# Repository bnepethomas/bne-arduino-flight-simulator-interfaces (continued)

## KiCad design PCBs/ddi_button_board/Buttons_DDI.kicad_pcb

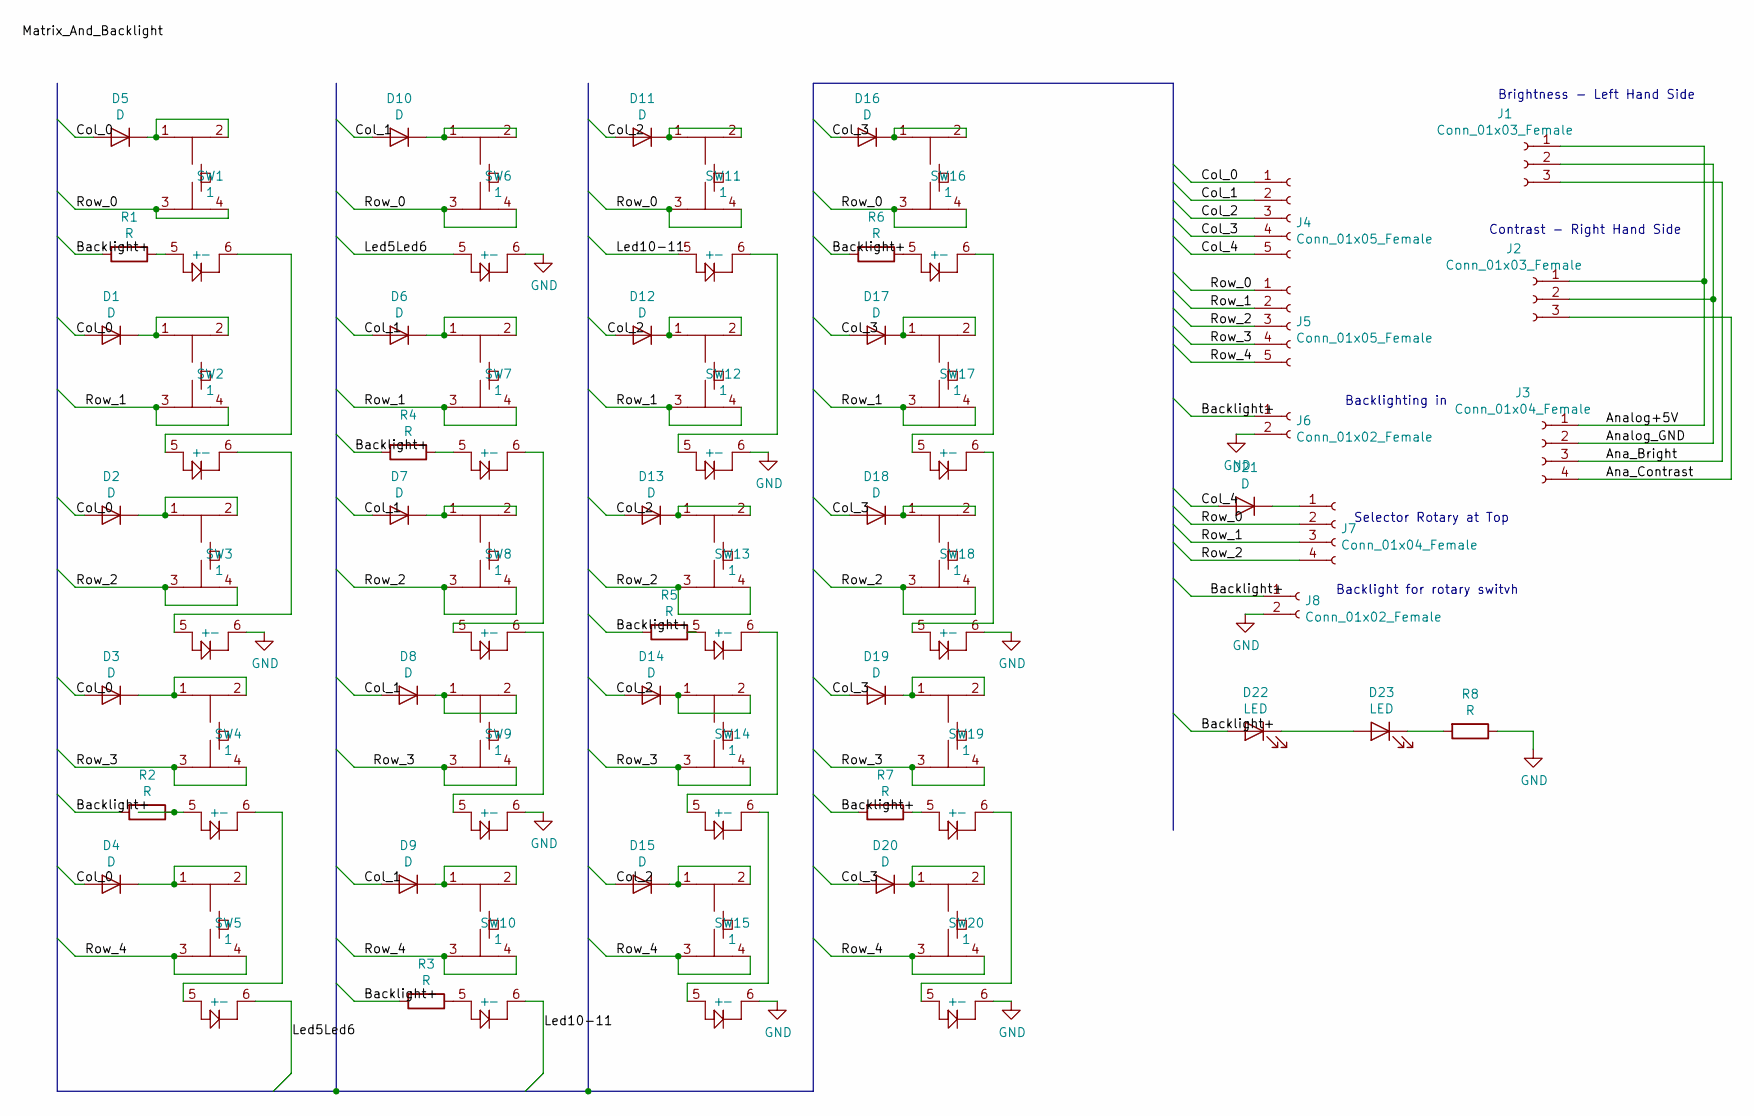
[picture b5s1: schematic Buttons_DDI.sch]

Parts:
D1, D2, D3, D4, D5, D6, D7, D8, D9, D10, D11, D12, D13, D14, D15, D16, D17, D18, D19, D20, D21: D; D_A-405_P7.62mm_Horizontal
D22, D23: LED; LED_D3.0mm
J1, J2: Conn_01x03_Female; PinHeader_1x03_P2.54mm_Vertical
J3, J7: Conn_01x04_Female; PinHeader_1x04_P2.54mm_Vertical
J4, J5: Conn_01x05_Female; PinHeader_1x05_P2.54mm_Vertical
J6, J8: Conn_01x02_Female; PinHeader_1x02_P2.54mm_Vertical
R1, R2, R3, R4, R5, R6, R7, R8: R; R_Axial_DIN0207_L6.3mm_D2.5mm_P7.62mm_Horizontal
SW1, SW2, SW3, SW4, SW5, SW6, SW7, SW8, SW9, SW10, SW11, SW12, SW13, SW14, SW15, SW16, SW17, SW18, SW19, SW20: 1; PT_Small_Tactile_Switch_With_LED

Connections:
/Ana_Bright: J1.3, J3.3
/Ana_Contrast: J2.3, J3.4
/Analog+5V: J1.1, J2.1, J3.1
/Analog_GND: J1.2, J2.2, J3.2
/Backlight+: D22.2 (A), J6.1, J8.1, R1.2, R2.2, R3.2, R4.2, R5.2, R6.2, R7.2
/Col_0: D1.2 (A), D2.2 (A), D3.2 (A), D4.2 (A), D5.2 (A), J4.1
/Col_1: D6.2 (A), D7.2 (A), D8.2 (A), D9.2 (A), D10.2 (A), J4.2
/Col_2: D11.2 (A), D12.2 (A), D13.2 (A), D14.2 (A), D15.2 (A), J4.3
/Col_3: D16.2 (A), D17.2 (A), D18.2 (A), D19.2 (A), D20.2 (A), J4.4
/Col_4: D21.2 (A), J4.5
/Led5Led6: SW5.6 (-), SW6.5 (+)
/Led10-11: SW10.6 (-), SW11.5 (+)
/Row_0: J5.1, J7.2, SW1.3, SW1.4, SW6.3, SW6.4, SW11.3, SW11.4, SW16.3, SW16.4
/Row_1: J5.2, J7.3, SW2.3, SW2.4, SW7.3, SW7.4, SW12.3, SW12.4, SW17.3, SW17.4
/Row_2: J5.3, J7.4, SW3.3, SW3.4, SW8.3, SW8.4, SW13.3, SW13.4, SW18.3, SW18.4
/Row_3: J5.4, SW4.3, SW4.4, SW9.3, SW9.4, SW14.3, SW14.4, SW19.3, SW19.4
/Row_4: J5.5, SW5.3, SW5.4, SW10.3, SW10.4, SW15.3, SW15.4, SW20.3, SW20.4
GND: J6.2, J8.2, R8.1, SW3.6 (-), SW6.6 (-), SW9.6 (-), SW12.6 (-), SW15.6 (-), SW18.6 (-), SW20.6 (-)
unnamed: D1.1 (K), SW2.1, SW2.2
unnamed: D2.1 (K), SW3.1, SW3.2
unnamed: D3.1 (K), SW4.1, SW4.2
unnamed: D4.1 (K), SW5.1, SW5.2
unnamed: D5.1 (K), SW1.1, SW1.2
unnamed: D6.1 (K), SW7.1, SW7.2
unnamed: D7.1 (K), SW8.1, SW8.2
unnamed: D8.1 (K), SW9.1, SW9.2
unnamed: D9.1 (K), SW10.1, SW10.2
unnamed: D10.1 (K), SW6.1, SW6.2
unnamed: D11.1 (K), SW11.1, SW11.2
unnamed: D12.1 (K), SW12.1, SW12.2
unnamed: D13.1 (K), SW13.1, SW13.2
unnamed: D14.1 (K), SW14.1, SW14.2
unnamed: D15.1 (K), SW15.1, SW15.2
unnamed: D16.1 (K), SW16.1, SW16.2
unnamed: D17.1 (K), SW17.1, SW17.2
unnamed: D18.1 (K), SW18.1, SW18.2
unnamed: D19.1 (K), SW19.1, SW19.2
unnamed: D20.1 (K), SW20.1, SW20.2
unnamed: D21.1 (K), J7.1
unnamed: D22.1 (K), D23.2 (A)
unnamed: D23.1 (K), R8.2
unnamed: R1.1, SW1.5 (+)
unnamed: R2.1, SW4.5 (+)
unnamed: R3.1, SW10.5 (+)
unnamed: R4.1, SW7.5 (+)
unnamed: R5.1, SW13.5 (+)
unnamed: R6.1, SW16.5 (+)
unnamed: R7.1, SW19.5 (+)
unnamed: SW1.6 (-), SW2.5 (+)
unnamed: SW2.6 (-), SW3.5 (+)
unnamed: SW4.6 (-), SW5.5 (+)
unnamed: SW7.6 (-), SW8.5 (+)
unnamed: SW8.6 (-), SW9.5 (+)
unnamed: SW11.6 (-), SW12.5 (+)
unnamed: SW13.6 (-), SW14.5 (+)
unnamed: SW14.6 (-), SW15.5 (+)
unnamed: SW16.6 (-), SW17.5 (+)
unnamed: SW17.6 (-), SW18.5 (+)
unnamed: SW19.6 (-), SW20.5 (+)

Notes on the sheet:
Brightness - Left Hand Side
Contrast - Right Hand Side
Selector Rotary at Top
Backlighting in
Backlight for rotary switvh

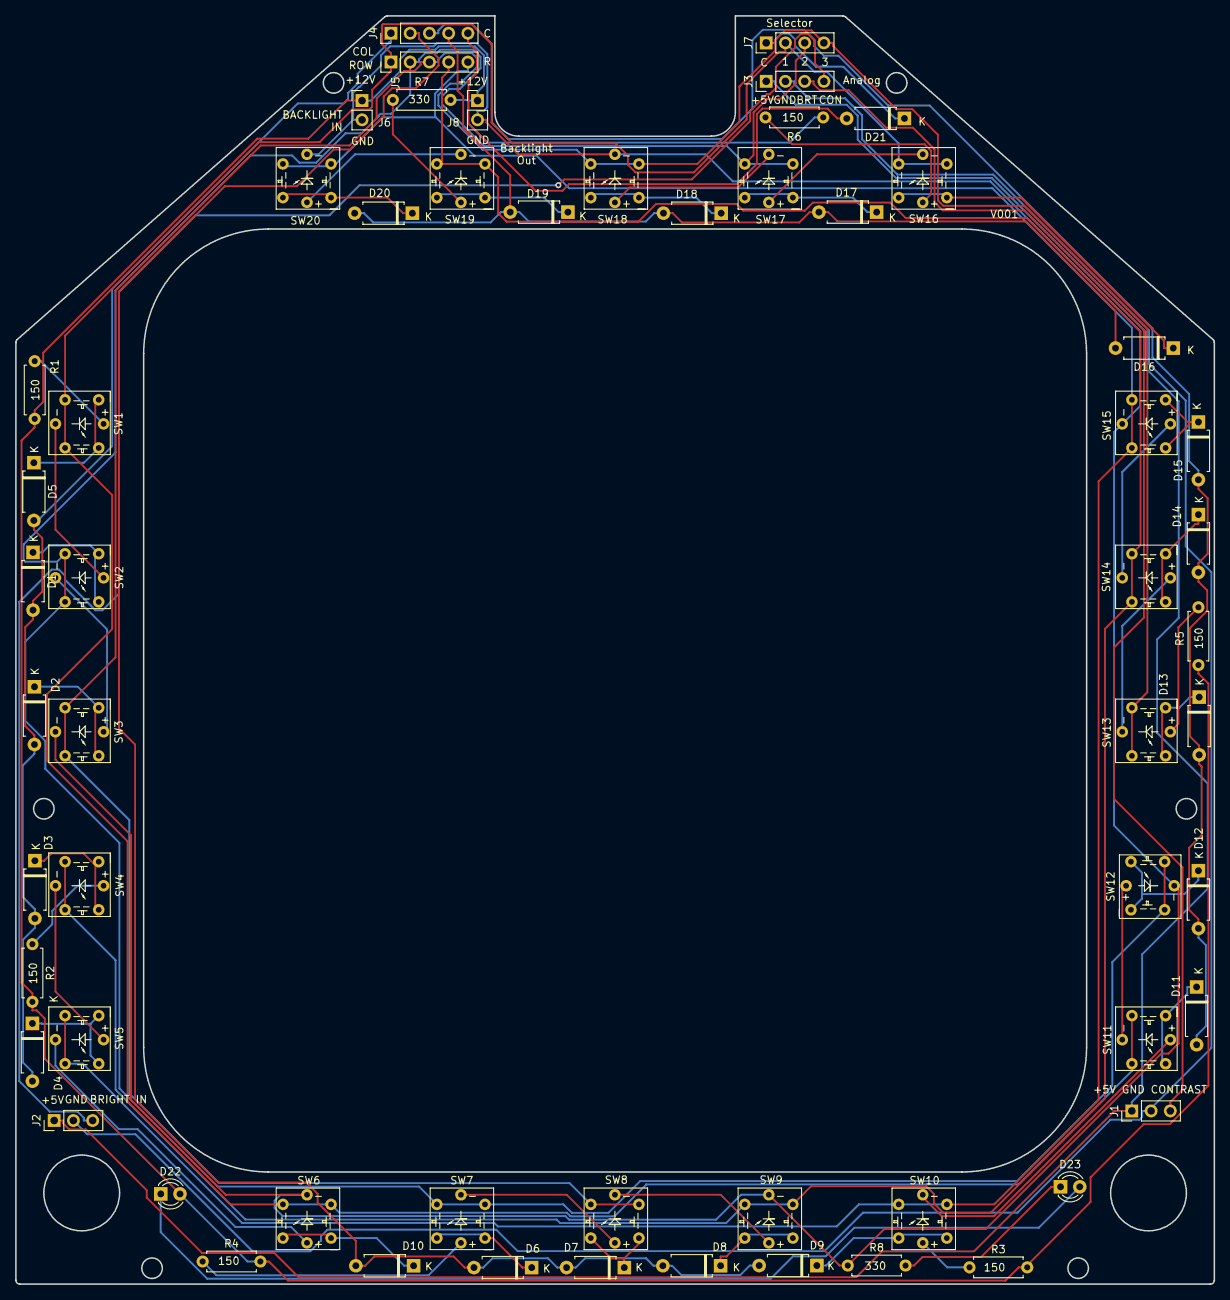
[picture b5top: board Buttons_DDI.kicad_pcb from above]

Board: 2 copper layers, 158.2 x 167.4 mm, 59 parts (0 on the bottom side), 59 nets.
